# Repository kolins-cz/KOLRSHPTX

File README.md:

KOLRSHPTX
=========

Another version of OpenLRS 1W transmitter
---------

Photos of older version
https://picasaweb.google.com/m.kolinsky/KOLRSHPTX12

Everything is basicaly same as other OpenLRS transmitters.

Main features:
* Board fits in this nice (expensive) aluminum box http://www.tme.eu/en/details/akg-55-24-100-me/enclosures-with-panel/fischer-elektronik/akg-55-24-100-me/
* Power switch
* Two power supplies possible, Traco or Recom 7805-like DCDC or cheap 3A DCDC http://www.ebay.com/itm/Mini-3A-DC-DC-Converter-Adjustable-Step-Down-Power-Supply-Module-Replace-LM2596-/390877057320
* Adjustable voltage with cheap 3A DCDC = adjustable RF output power
* Reverse polarity protection
* Power from USB-serial may or may not be connected
* Standard 6pin ISP header
* Improved cooling of RFM23BP
* Open source!

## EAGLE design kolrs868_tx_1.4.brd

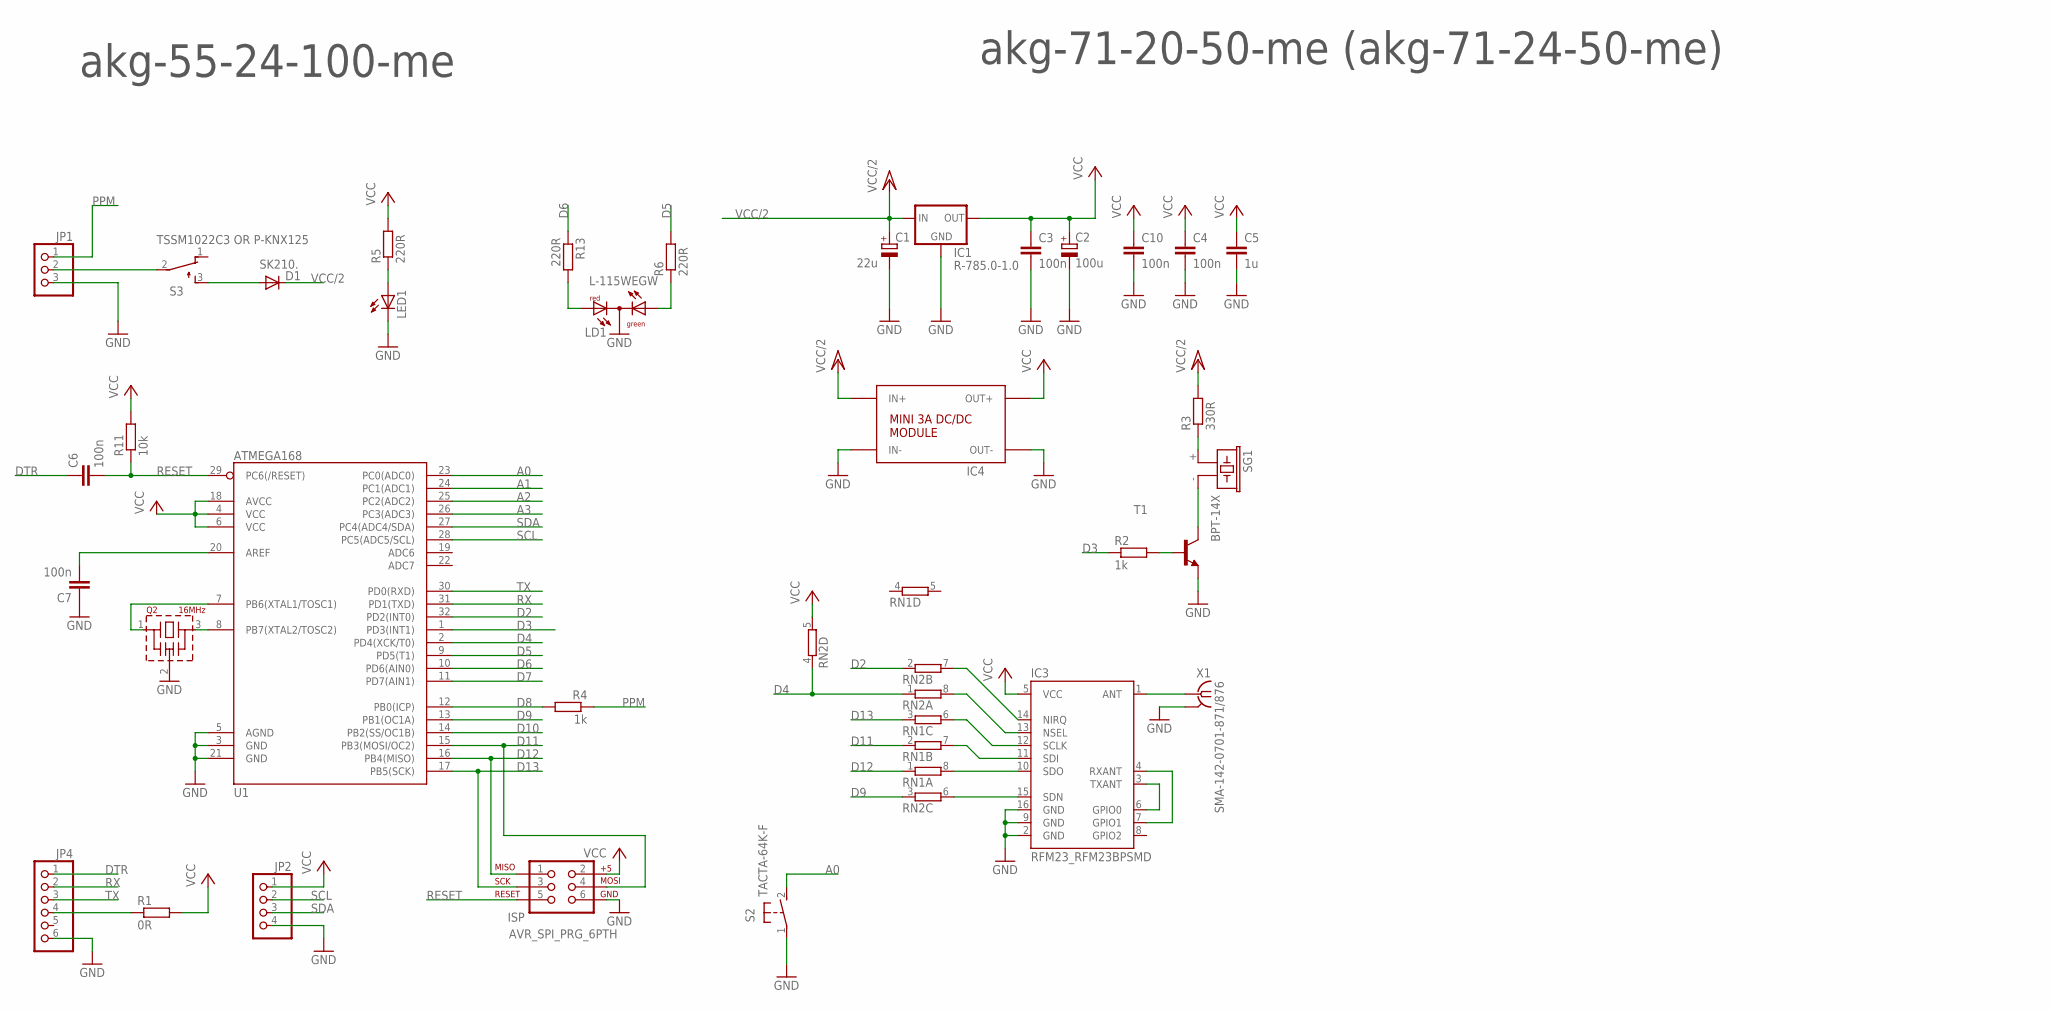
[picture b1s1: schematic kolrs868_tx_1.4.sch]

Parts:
C1: 22u; SMC_B
C2: 100u; SMC_B
C3, C4, C6, C7, C10: 100n; M0805
C5: 1u; C1206
D1: SK210.; SMB
IC1: R-785.0-1.0; 78XX_RECOM
IC3: RFM23_RFM23BPSMD; RFM23_RFM23BP-S2
IC4: MINI_3A_DCDC
ISP: AVR_SPI_PRG_6PTH; 2X3
JP1: PINHD-1X3; 1X03
JP2: PINHD-1X4; 1X04
JP4: PINHD-1X6; 1X06
LD1: L-115WEGW; DUOLED-C-5MM
LED1: LEDCHIPLED_1206; CHIPLED_1206
Q2: 16MHz; CSTLS_G8
R1: 0R; M0805
R2, R4: 1k; M0805
R3: 330R; M0805
R5, R6, R13: 220R; M0805
R11: 10k; M0805
RN1, RN2: 4R-NCAY16; CAY16
S2: TACTA-64K-F; B3F-31XX
S3: TSSM1022C3 OR P-KNX125; TL3XWO
SG1: BPT-14X; F/CM12P
T1: BC848-NPN-SOT23-BEC; SOT23-BEC
U1: ATMEGA168; TQFP32-08
X1: SMA-142-0701-871/876; J502-ND-142-0701-871/876

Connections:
A0: S2.2 (S), U1.23 (PC0(ADC0))
A1: U1.24 (PC1(ADC1))
A2: U1.25 (PC2(ADC2))
A3: U1.26 (PC3(ADC3))
D2: RN2.2 (1), U1.32 (PD2(INT0))
D3: R2.1, U1.1 (PD3(INT1))
D4: RN2.1, RN2.4 (1), U1.2 (PD4(XCK/T0))
D5: R6.2, U1.9 (PD5(T1))
D6: R13.1, U1.10 (PD6(AIN0))
D7: U1.11 (PD7(AIN1))
D8: R4.2, U1.12 (PB0(ICP))
D9: RN2.3 (1), U1.13 (PB1(OC1A))
D10: U1.14 (PB2(SS/OC1B))
D11: ISP.4, RN1.2 (1), U1.15 (PB3(MOSI/OC2))
D12: ISP.1, RN1.1, U1.16 (PB4(MISO))
D13: ISP.3, RN1.3 (1), U1.17 (PB5(SCK))
DTR: C6.1, JP4.1
GND: C1.-, C2.-, C3.2, C4.2, C5.2, C7.1, C10.2, IC1.GND, IC3.2 (GND), IC3.9 (GND), IC3.16 (GND), IC4.1 (IN-), IC4.2 (IN-), IC4.7 (OUT-), IC4.8 (OUT-), ISP.6, JP1.3, JP2.4, JP4.6, LD1.C, LED1.C, Q2.2 (VSS), S2.1, T1.E, U1.3 (GND), U1.5 (AGND), U1.21 (GND), X1.G@1 (GND), X1.G@2 (GND), X1.G@3 (GND), X1.G@4 (GND)
unnamed: C7.2, U1.20 (AREF)
unnamed: IC3.3 (TXANT), IC3.6 (GPIO0)
unnamed: IC3.4 (RXANT), IC3.7 (GPIO1)
unnamed: IC3.1 (ANT), X1.1
unnamed: LD1.AR, R13.2
unnamed: Q2.1, U1.7 (PB6(XTAL1/TOSC1))
unnamed: Q2.3, U1.8 (PB7(XTAL2/TOSC2))
unnamed: LD1.AX (AG), R6.1
unnamed: D1.A, S3.3 (S)
unnamed: R2.2, T1.B
unnamed: SG1.- (2), T1.C
unnamed: R3.1, SG1.+ (1)
unnamed: JP1.2, S3.2
unnamed: LED1.A, R5.1
unnamed: JP4.4, R1.1
unnamed: IC3.10 (SDO), RN1.8 (2)
unnamed: IC3.11 (SDI), RN1.7 (2)
unnamed: IC3.12 (SCLK), RN1.6 (2)
unnamed: IC3.15 (SDN), RN2.6 (2)
unnamed: IC3.13 (NSEL), RN2.8 (2)
unnamed: IC3.14 (NIRQ), RN2.7 (2)
PPM: JP1.1, R4.1
RESET: C6.2, ISP.5, R11.1, U1.29 (PC6(/RESET))
RX: JP4.2, U1.31 (PD1(TXD))
SCL: JP2.2, U1.28 (PC5(ADC5/SCL))
SDA: JP2.3, U1.27 (PC4(ADC4/SDA))
TX: JP4.3, U1.30 (PD0(RXD))
VCC: C2.+, C3.1, C4.1, C5.1, C10.1, IC1.OUT, IC3.5 (VCC), IC4.5 (OUT+), IC4.6 (OUT+), ISP.2, JP2.1, R1.2, R5.2, R11.2, RN2.5 (2), U1.4 (VCC), U1.6 (VCC), U1.18 (AVCC)
VCC/2: C1.+, D1.C, IC1.IN, IC4.3 (IN+), IC4.4 (IN+), R3.2

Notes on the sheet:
akg-71-20-50-me (akg-71-24-50-me)
akg-55-24-100-me

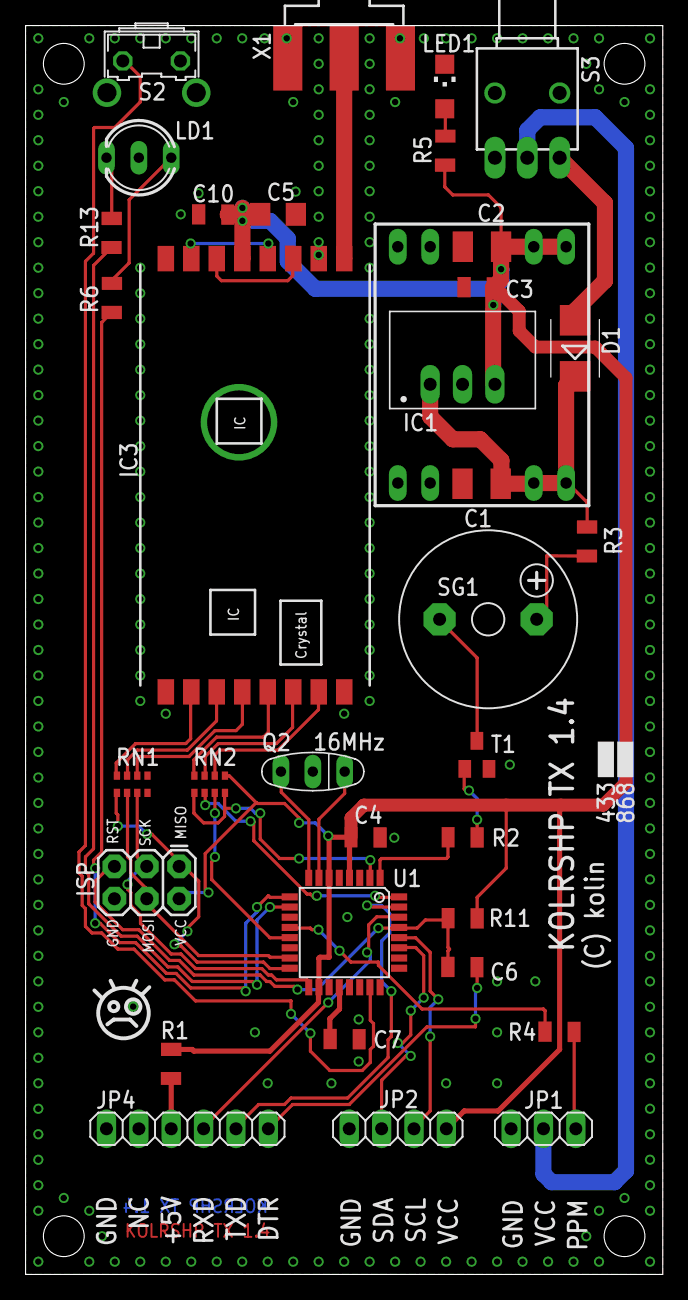
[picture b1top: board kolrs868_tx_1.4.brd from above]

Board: 2 copper layers, 50.0 x 98.0 mm, 35 parts (0 on the bottom side), 42 nets.

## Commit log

2014-08-10 :lollipop: Added .gitattributes & .gitignore files
2014-08-10 Initial version
2014-08-10 Added readme
